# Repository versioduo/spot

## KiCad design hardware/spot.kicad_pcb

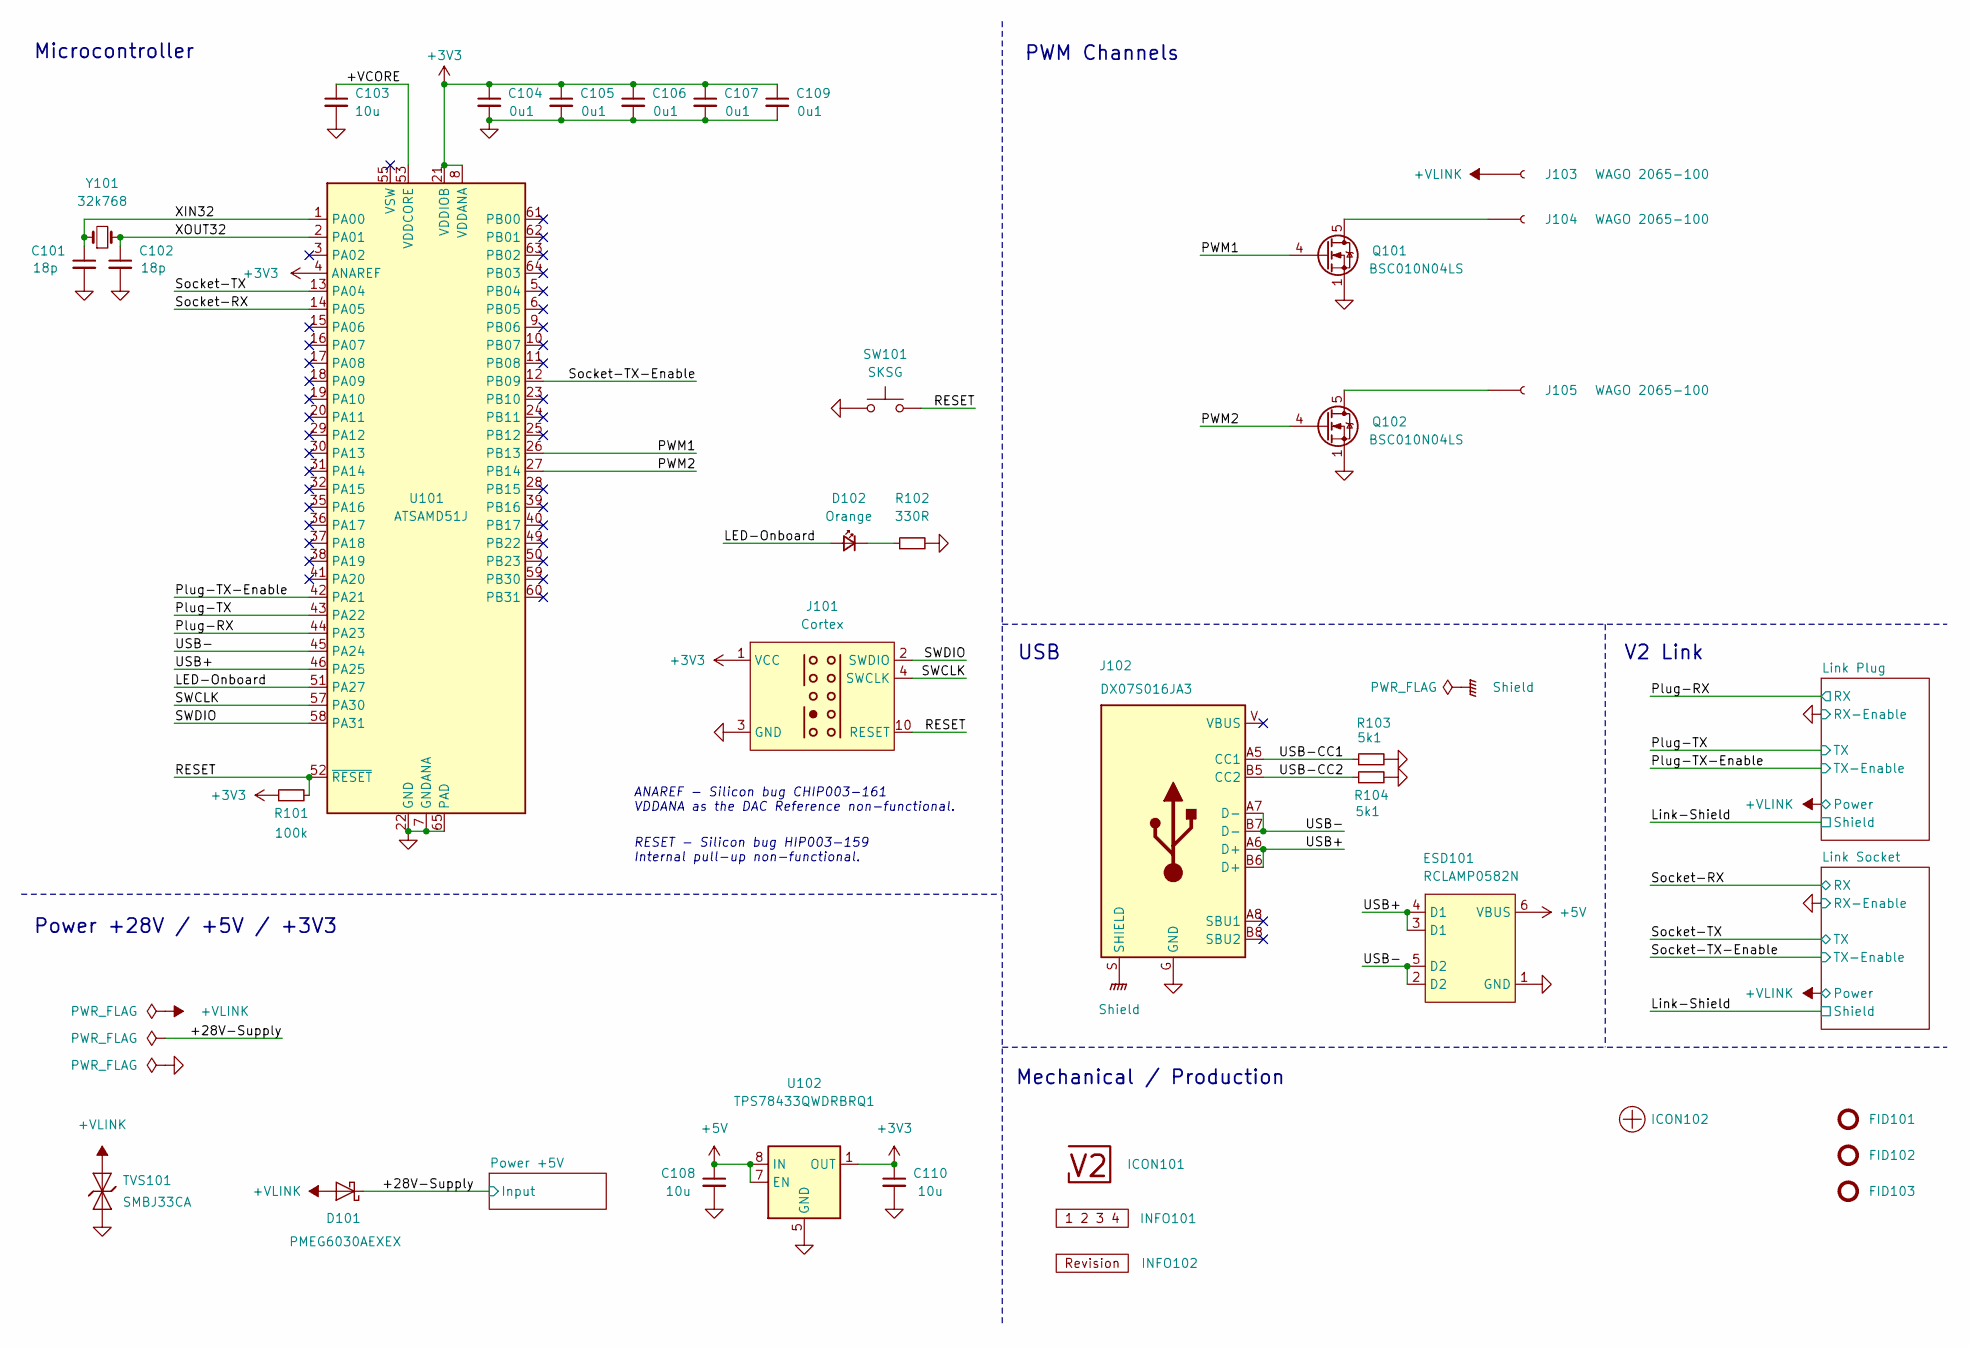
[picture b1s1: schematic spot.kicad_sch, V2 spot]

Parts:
C101, C102: 18p; C_1608; Rating 50V; Mouser 810-CGA3E2C0G1H180J
C103: 10u; C_1608; Rating 10V; Mouser 810-C1608X6S1A106M
C104, C105, C106, C107, C109: 0u1; C_1608; Rating 50V; Mouser 810-CGA3E2X7R1H104MA
C108, C110: 10u; C_2012; Rating 25V; Mouser 810-C2012X5R1E106K
D101: PMEG6030AEXEX; D_SOD-123HP; Rating 60V; Mouser 771-PMEG6030AEXEX
D102: Orange; LED_1608; Rating 605nm; Mouser 755-SML-D12D1WT86
ESD101: RCLAMP0582N; SLP1210N6; Rating 20kV; Mouser 947-RCLAMP0582N.TCT
FID101, FID102, FID103: Fiducial_Paste; Fiducial_0.5mm_Mask1mm_Paste
ICON101: V2-logo; Logo_Small
ICON102: Plus; Plus_Small
INFO101: Layer_Numbers-6
INFO102: Revision
J101: Cortex
J102: DX07S016JA3; JAE_DX07S016JA3; Rating USB2.0; Mouser 656-DX07S016JA3R1500
J103, J104, J105: WAGO 2065-100; 2065-100; Rating 9A
Q101, Q102: BSC010N04LS; TDSON-8-FL; Rating 40V; Mouser 726-BSC010N04LS
R101: 100k; R_1608; Rating 100mW; Mouser 71-CRCW0603100KFKEAC
R102: 330R; R_1608; Rating 100mW; Mouser 71-CRCW0603330RFKEAC
R103, R104: 5k1; R_1608; Rating 100mW; Mouser 71-CRCW06035K10FKEAC
SW101: SKSG; Rating 1.6N; Mouser 688-SKSGACE010
TVS101: SMBJ33CA; D_SMB; Rating 33V; Mouser 652-SMBJ33CA-Q
U101: ATSAMD51J; QFN-64-1EP_9x9mm_P0.5mm_EP4.8x4.8mm_ThermalVias; Rating Cortex-M4F; Mouser 556-ATSAMD51J19AMU
U102: TPS78433QWDRBRQ1; VSON-8-1_3x3mm_P0.65_EP1.65x2.4mm; Rating 300mA; Mouser 595-TPS78433QWDRBRQ1
Y101: 32k768; Crystal_SMD_3215-2Pin_3.2x1.5mm; Rating 10ppm; Mouser 815-ABS0716632.768KT

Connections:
+3V3: C104.1, C105.1, C106.1, C107.1, C109.1, C110.1, J101.1 (VCC), R101.1, U101.4 (ANAREF), U101.8 (VDDANA), U101.21 (VDDIOB), U101.34 (VDDIO), U101.48 (VDDIO), U101.56 (VDDIO), U102.1 (OUT); also elsewhere on the board
+5V: C108.1, ESD101.6 (VBUS), U102.6 (EN), U102.7 (EN), U102.8 (IN); also elsewhere on the board
/+28V-Supply: D101.1 (K); also elsewhere on the board
/+VCORE: C103.1, U101.53 (VDDCORE)
/+VLINK: D101.2 (A), J103.1, TVS101.2 (A); also elsewhere on the board
/LED-Onboard: D102.2 (A), U101.51 (PA27)
/PWM1: Q101.4 (G), U101.26 (PB13)
/PWM2: Q102.4 (G), U101.27 (PB14)
/Plug-RX: U101.44 (PA23); also elsewhere on the board
/Plug-TX: U101.43 (PA22); also elsewhere on the board
/Plug-TX-Enable: U101.42 (PA21); also elsewhere on the board
/RESET: J101.10 (RESET), R101.2, SW101.2, U101.52 (~RESET)
/SWCLK: J101.4 (SWCLK), U101.57 (PA30)
/SWDIO: J101.2 (SWDIO), U101.58 (PA31)
/Shield: J102.S (SHIELD)
/Socket-RX: U101.14 (PA05); also elsewhere on the board
/Socket-TX: U101.13 (PA04); also elsewhere on the board
/Socket-TX-Enable: U101.12 (PB09); also elsewhere on the board
/USB+: ESD101.3 (D1), ESD101.4 (D1), J102.A6 (D+), J102.B6 (D+), U101.46 (PA25)
/USB-: ESD101.2 (D2), ESD101.5 (D2), J102.A7 (D-), J102.B7 (D-), U101.45 (PA24)
/USB-CC1: J102.A5 (CC1), R103.1
/USB-CC2: J102.B5 (CC2), R104.1
/XIN32: C101.1, U101.1 (PA00), Y101.1
/XOUT32: C102.1, U101.2 (PA01), Y101.2
GND: C101.2, C102.2, C103.2, C104.2, C105.2, C106.2, C107.2, C108.2, C109.2, C110.2, ESD101.1 (GND), J101.3 (GND), J101.5 (GND), J102.G (GND), Q101.1 (S), Q102.1 (S), R102.2, R103.2, R104.2, SW101.1, TVS101.1 (K), U101.7 (GNDANA), U101.22 (GND), U101.33 (GND), U101.47 (GND), U101.54 (GND), U101.65 (PAD), U102.5 (GND), U102.9 (GND); also elsewhere on the board
unnamed: D102.1 (K), R102.1
unnamed: J104.1, Q101.5 (D)
unnamed: J105.1, Q102.5 (D)

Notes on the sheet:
﻿ANAREF - Silicon bug CHIP003-161 VDDANA as the DAC Reference non-functional.
PWM Channels
RESET - ﻿Silicon bug HIP003-159 Internal pull-up non-functional.
USB
Mechanical / Production
Power +28V / +5V / +3V3
V2 Link
Microcontroller

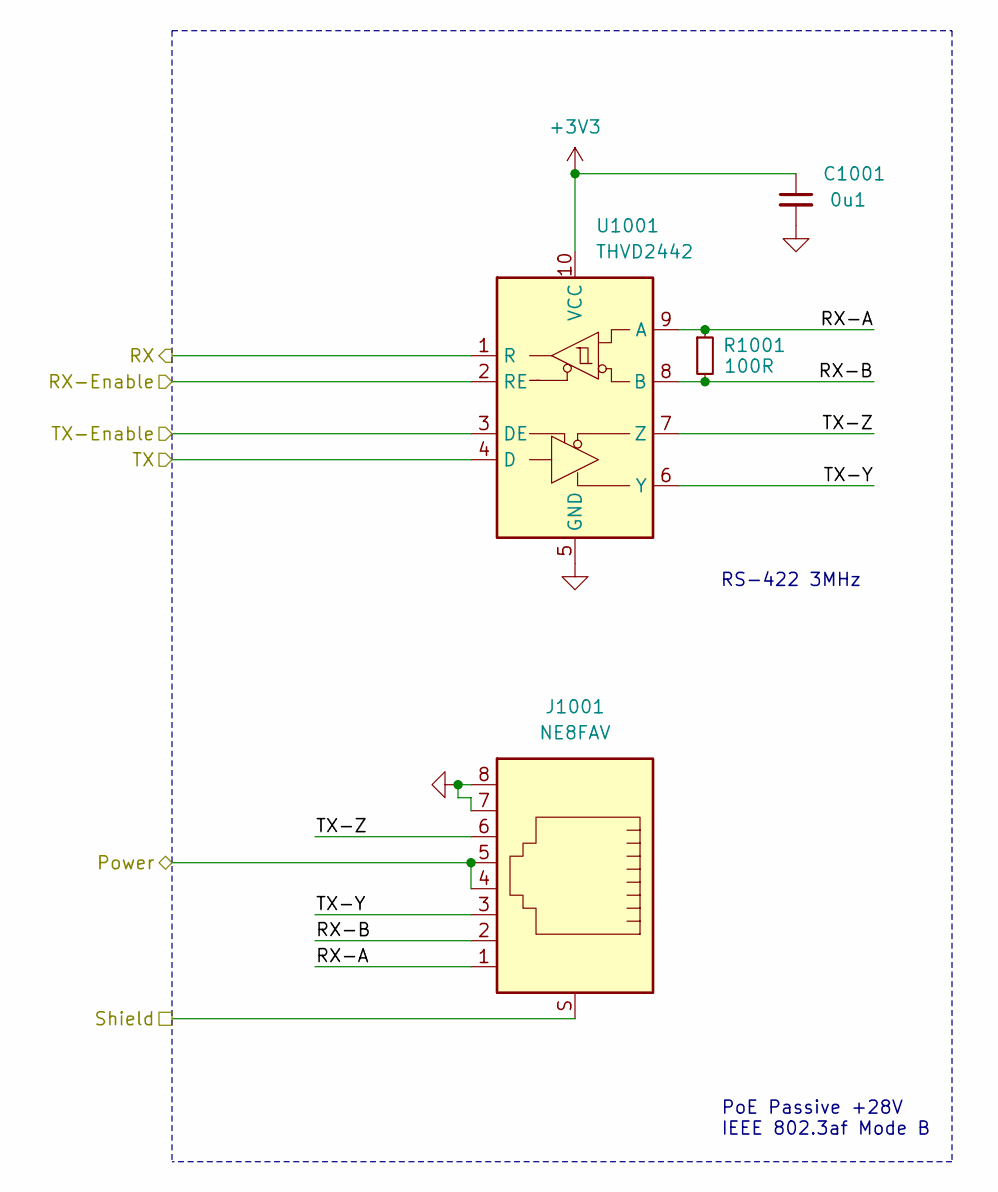
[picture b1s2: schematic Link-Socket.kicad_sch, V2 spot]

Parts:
C1001: 0u1; C_1608; Rating 50V; Mouser 810-CGA3E2X7R1H104MA
J1001: NE8FAV; Rating CAT5e; Mouser 568-NE8FAV-SD
R1001: 100R; R_1608; Rating 330mW; Mouser 71-CRCW0603100RFKEAH
U1001: THVD2442; VSON-10-4-1EP_3x3mm_P0.5mm_EP1.65x2.4mm_ThermalVias; Rating 20Mbps; Mouser 595-THVD2442DRCR

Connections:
+3V3: C1001.1, U1001.10 (VCC); also elsewhere on the board
/+VLINK: J1001.4, J1001.5; also elsewhere on the board
/Link Socket/RX-A: J1001.1, R1001.1, U1001.9 (A)
/Link Socket/RX-B: J1001.2, R1001.2, U1001.8 (B)
/Link Socket/TX-Y: J1001.3, U1001.6 (Y)
/Link Socket/TX-Z: J1001.6, U1001.7 (Z)
/Link-Shield: J1001.S; also elsewhere on the board
/Socket-RX: U1001.1 (R); also elsewhere on the board
/Socket-TX: U1001.4 (D); also elsewhere on the board
/Socket-TX-Enable: U1001.3 (DE); also elsewhere on the board
GND: C1001.2, J1001.7, J1001.8, U1001.2 (RE), U1001.5 (GND), U1001.11 (GND); also elsewhere on the board

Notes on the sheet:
PoE Passive +28V IEEE 802.3af Mode B
RS-422 3MHz

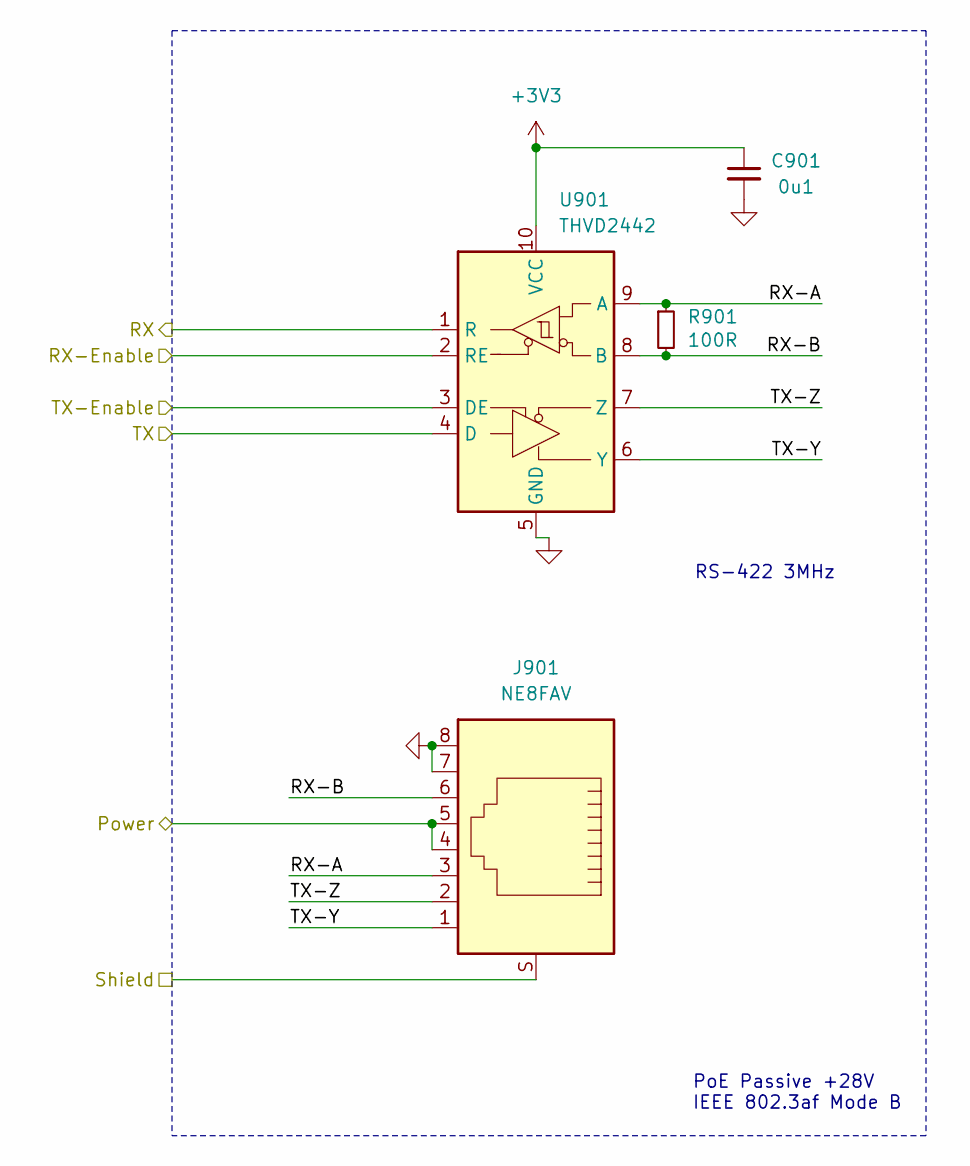
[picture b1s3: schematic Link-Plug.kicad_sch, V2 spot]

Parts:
C901: 0u1; C_1608; Rating 50V; Mouser 810-CGA3E2X7R1H104MA
J901: NE8FAV; Rating CAT5e; Mouser 568-NE8FAV-SD
R901: 100R; R_1608; Rating 330mW; Mouser 71-CRCW0603100RFKEAH
U901: THVD2442; VSON-10-4-1EP_3x3mm_P0.5mm_EP1.65x2.4mm_ThermalVias; Rating 20Mbps; Mouser 595-THVD2442DRCR

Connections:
+3V3: C901.1, U901.10 (VCC); also elsewhere on the board
/+VLINK: J901.4, J901.5; also elsewhere on the board
/Link Plug/RX-A: J901.3, R901.1, U901.9 (A)
/Link Plug/RX-B: J901.6, R901.2, U901.8 (B)
/Link Plug/TX-Y: J901.1, U901.6 (Y)
/Link Plug/TX-Z: J901.2, U901.7 (Z)
/Link-Shield: J901.S; also elsewhere on the board
/Plug-RX: U901.1 (R); also elsewhere on the board
/Plug-TX: U901.4 (D); also elsewhere on the board
/Plug-TX-Enable: U901.3 (DE); also elsewhere on the board
GND: C901.2, J901.7, J901.8, U901.2 (RE), U901.5 (GND), U901.11 (GND); also elsewhere on the board

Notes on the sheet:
RS-422 3MHz
PoE Passive +28V IEEE 802.3af Mode B

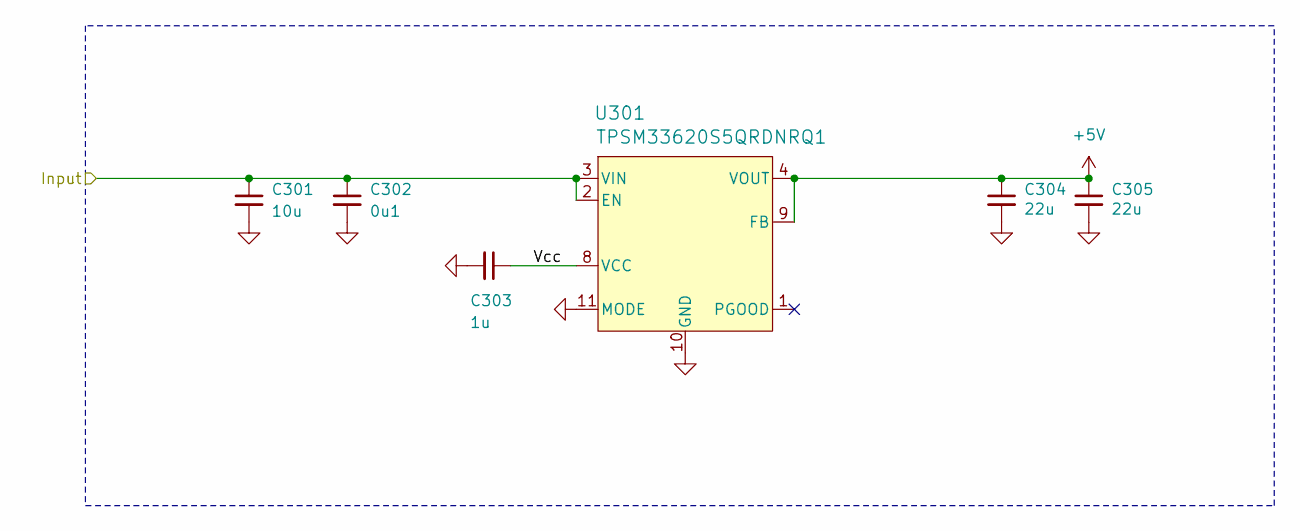
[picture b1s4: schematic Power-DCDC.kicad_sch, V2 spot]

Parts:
C301: 10u; C_3225; Rating 50V; Mouser 810-CNC6P1X7R1H106K2
C302: 0u1; C_1608; Rating 50V; Mouser 810-CGA3E2X7R1H104MA
C303: 1u; C_1608; Rating 50V; Mouser 810-CGA3E3X7R1H105K0
C304, C305: 22u; C_3225; Rating 25V; Mouser 810-CGA6P3X7R1E226M5
U301: TPSM33620S5QRDNRQ1; QFN-11; Rating 2A; Mouser 595-SM33620S5QRDNRQ1

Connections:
+5V: C304.1, C305.1, U301.4 (VOUT), U301.9 (FB); also elsewhere on the board
/+28V-Supply: C301.1, C302.1, U301.2 (EN), U301.3 (VIN); also elsewhere on the board
/Power +5V/Vcc: C303.1, U301.8 (VCC)
GND: C301.2, C302.2, C303.2, C304.2, C305.2, U301.10 (GND), U301.11 (MODE); also elsewhere on the board

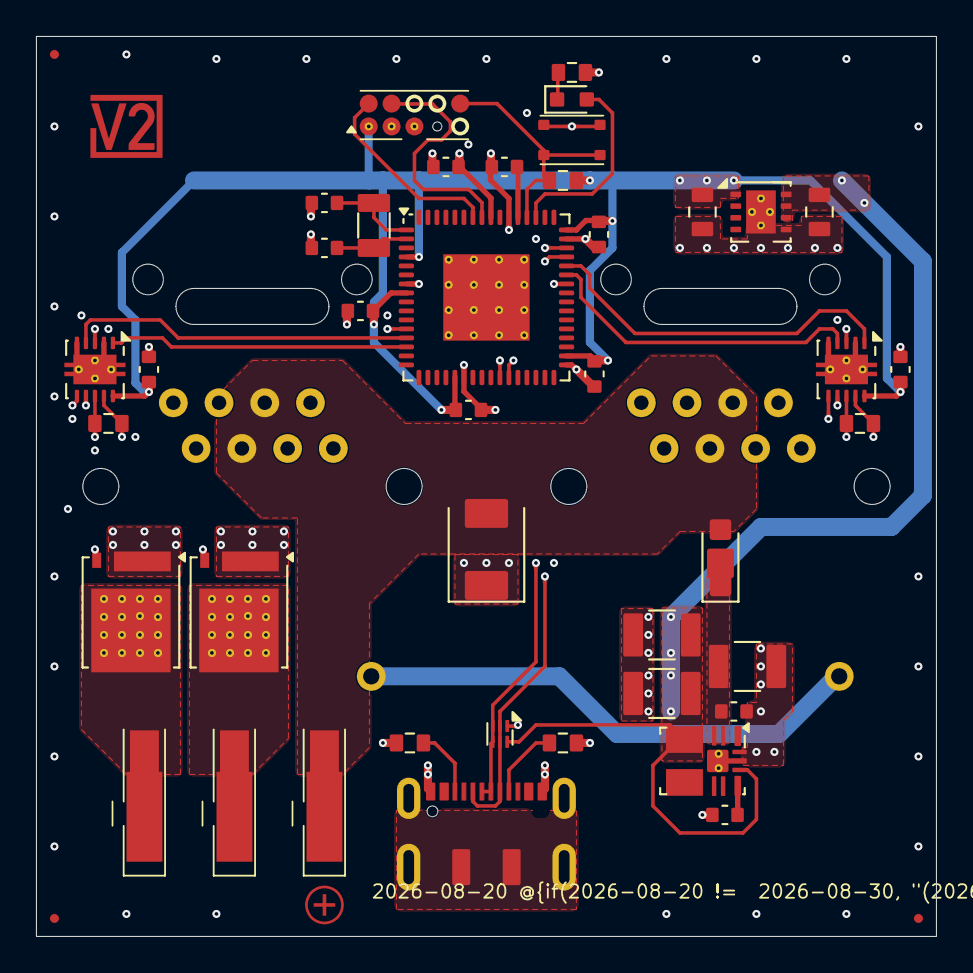
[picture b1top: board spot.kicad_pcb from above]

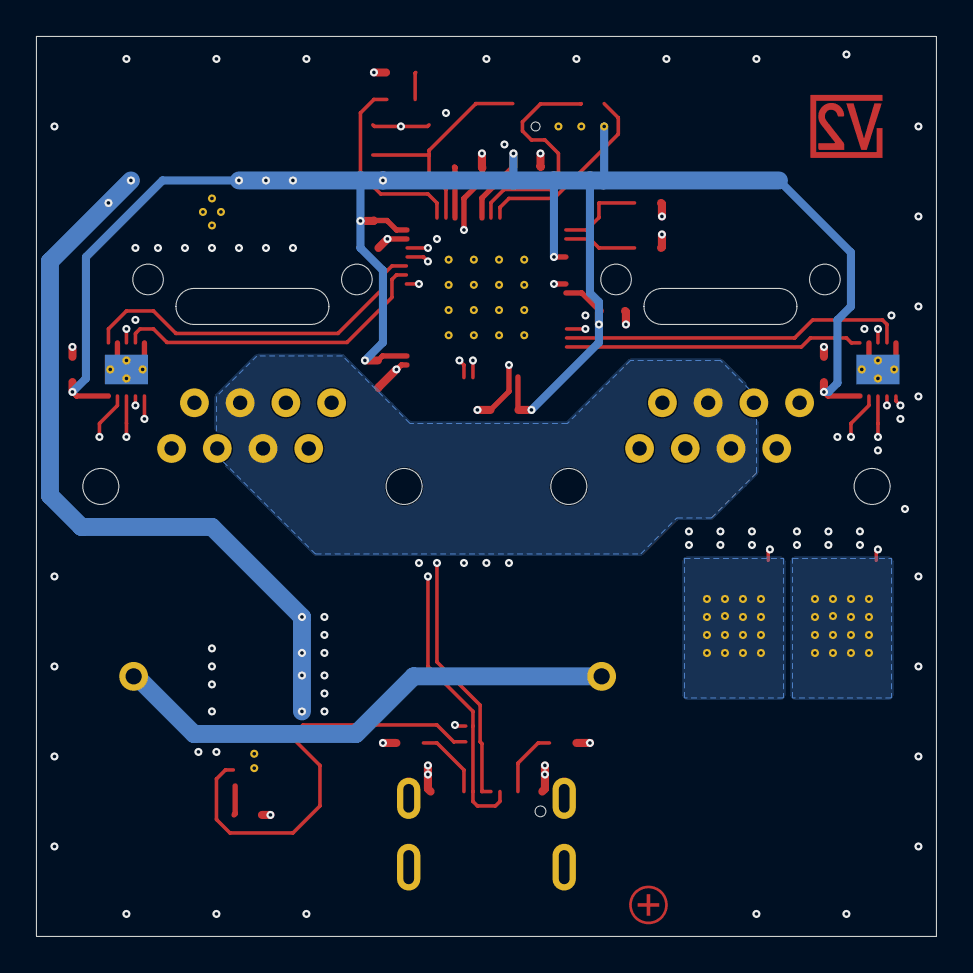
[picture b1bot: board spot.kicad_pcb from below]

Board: 6 copper layers, 50.0 x 50.0 mm, 50 parts (2 on the bottom side), 37 nets.

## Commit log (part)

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2026-06-30 Import
